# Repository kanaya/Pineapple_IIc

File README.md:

# Pineapple IIc

Edition 2.0.0 for Pineapple IIc 2.0.0

## Congratulations!

You’ve got the latest version of Pineapple Computer named _Pineapple IIc._ But what is Pineapple Computer? Well, it is a MIDI computer that can convert analog signals to MIDI (digital) signal. Now you may want to ask, I guess, what is it for? The Pineapple Computer is an artist-friendly super-easy-to-use computer! You plug power, sensor, MIDI instrument, and boom! Everything is set up.

## How to set up (Hardware)

### Basics

Install the following components.

| Name        | Component         | Note                              |
|-------------|-------------------|-----------------------------------|
| C1          | 47u               |                                   |
| C2          | 10u               |                                   |
| C3-6        | 0.1u              |                                   |
| D1          | 1N4148            |                                   |
| DC12V       | DC Jack           |                                   |
| IC1         | 74LS07            |                                   |
| JP2         | Pinheader 1x3p    | **Bridge top and mid pins**       |
| LED1        | Vf=2.2 If=20m     |                                   |
| MC1         | Arduino Micro 5V  |                                   |
| MIDI-OUT    | DIN 5p            |                                   |
| OK1         | TLP552            |                                   |
| R3-6        | 220               |                                   |
| RN1         | 330               |                                   |
| RN2         | 10k               | Using pin sockets is recommended. |
| SV1         | ML 16p            |                                   |
| VREG1       | 12V to 5V         |                                   |

...To be re-written.

### Non-basic usage

You can drive a relay, I2C devices, and TLC5940 PWM driver by installing some other components on Pineapple IIc. Also you can replace some connectors so that you can use panel mounted connectors and install Pineapple IIc board in a case. For more detail, please read _Extending Pineapple IIc_.

## How to set up (Software)

Install _Pineapple IIc Basic_ sketch to run Pineapple IIc in _Basic_ mode.

## How to play

Connect the following plugs.

* DC---Supply DC 12V to DC Jack connector.
* MIDI---Connect Pineapple IIc's MIDI OUT and your instrument's MIDI IN.
* Sensors---To be written.

## Extending Pineapple IIc

### To use relay

Install the following components as well as _Basic_ components.

| Item        | Name | Spec.      | # |  Note |
|-------------|------|------------|---|-------|
| Transistor  | T1   | 2SC1815    | 1 |       |
| Diode       | D2   | 1N4148     | 1 |       |
| Resistor    | R5-6 | 10k        | 2 |       |
| Relay       | K1   | G5V-1 DC5V | 1 |       |
| Con.        | Relay | PH 3p     | 1 |       |

Also you need to **bridge 7-8 of JP1.**

### To use I2C

Install the following components as well as _Basic_ components.

| Item                   | Name | Spec.      | # |  Note                       |
|------------------------|------|------------|---|-----------------------------|
| Signal level converter | IC2  | PCA9517ADP | 1 | Put A-side up, B-side down. |
| Resistor               | R7-8 | 6.8k       | 2 |                             |
| Con.                   | I2C  | SH 5p      | 1 | D7 operates at **5V.**      |

You need to **un-bridge 1-5, 2-6, 3-7 of JP1.** (D2/SDA and D7 are connected to SW1, and D3PWM/SCL is connected to PWM0 via JP1.)

### To use RST

Install the following components at back side as well as _Basic_ components.

| Item | Name       | Spec.   | # |  Note |
|------|------------|---------|---|-------|
| Con. | RST (Back) | PH 2p   | 1 |       |

### To use LIGHTDRIVE

Install the following components as well as _Basic_ components **except for SW1.** Since Arduino's D8 and D12 pins share SW1 connections and LIGHTDRIVE pins, you need to remove SW1.

| Item | Name       | Spec.        | # |  Note |
|------|------------|--------------|---|-------|
| Con. | LIGHTDRIVE | Pinheader 7p | 1 |       |

The LIGHTDRIVE pinouts are:

| Lightdrive | Meaning | Arduino Pin |
|------------|---------|-------------|
| 1          | Vcc     |             |
| 2          | GND     |             |
| 3          | GSCLCK  | D5PWM       |
| 4          | BLANK   | D8          |
| 5          | XLAT    | D12         |
| 6          | SCLCK   | SCLK        |
| 7          | SIN     | MOSI        |

### To use extra GND pins

Install the following components at back side as well as _Basic_ components.

| Item | Name       | Spec.                 | # |  Note |
|------|------------|-----------------------|---|-------|
| Con. | GND (back) | Pinheader/socket 2x3p | 1 |       |

### To use panel-mounted MIDI connector

Install the following components at back side as well as _Basic_ components.

| Item | Name        | Spec.        | # |  Note |
|------|-------------|--------------|---|-------|
| Con. | MIDI (back) | PH 5p        | 1 |       |

### To use panel-mounted DC Jack

Install one of the following components as well as _Basic_ components.

| Item | Name        | Spec.        | # |  Note |
|------|-------------|--------------|---|-------|
| Con. | PWR1        | Pinheader 2p | 1 |       |
| Con. | PWR2 (back) | PH 2p        | 1 |       |

### To use XOUT

XOUT is designed for extra MIDI OUT capability. It is a direct output of Open Collector so that you may want to install 220-ohm resistor for use as MIDI OUT.

Install the following components as well as _Basic_ components.

| Item | Name | Spec.        | # |  Note |
|------|------|--------------|---|-------|
| Con. | XOUT | Pinheader 5p | 1 |       |

### To use DIGITAL extension

You can hook L1-L7 driver pins by using DIGITAL pins. It also provides +3.3V DC.

Install the following components as well as _Basic_ components.

| Item | Name   | Spec.        | # |  Note |
|------|--------|--------------|---|-------|
| Con. | DIGITL | Pinheader 9p | 1 |       |

### To stack multiple cards

To stack multiple cards, you can do one of the following options.

* Use spacer. _Pineapple IIc_ has four M2 holes at each corners ((3, 3), (88, 3) (88, 52), (3, 52) mm).
* Use Pinheaders of Vcc (bottom left), 3V3 (bottom right), _Pogo_ (top right), Vcc (top left) and perhaps GND (next to the Vcc at top left).

## Technical notes

### Arduino Pinout

| Arduino Micro | Signal     | JP1                               |
|---------------|------------|-----------------------------------|
| RX            | MIDI IN    |                                   |
| TX            | MIDI OUT   |                                   |
| D2/SDA        | SW0/SDA    | 3-4, open to use I2C              |
| D3PWM/SCL     | PWM0/SCL   |                                   |
| D4/A6         | A6         |                                   |
| D5PWM         | PWM1       |                                   |
| D6PWM/A7      | PWM2       |                                   |
| D7            | SW1        | 5-6, open to use D7 independently |
| D8/A8         | SW2        |                                   |
| D9PWM/A9      | PWM3       |                                   |
| D10PWM/A10    | PWM4       |                                   |
| D11PWM        | PWM5       |                                   |
| D12/A11       | SW3        |                                   |
| D13PWM        | PWM6/Relay | 7-8, close to use relay           |
| A0-5          | A0-5       |                                   |

### JP1 Pinout

| JP1 | Signal                 | JP1 | Signal |
|-----|------------------------|-----|--------|
| 1   | Level Converter Enable | 2   | GND    |
| 3   | D2SDA (SW0/SDA)        | 4   | SW0    |
| 5   | D7 (SW1)               | 6   | SW1    |
| 7   | D13PWM (PWM6/Relay)    | 8   | Relay  |

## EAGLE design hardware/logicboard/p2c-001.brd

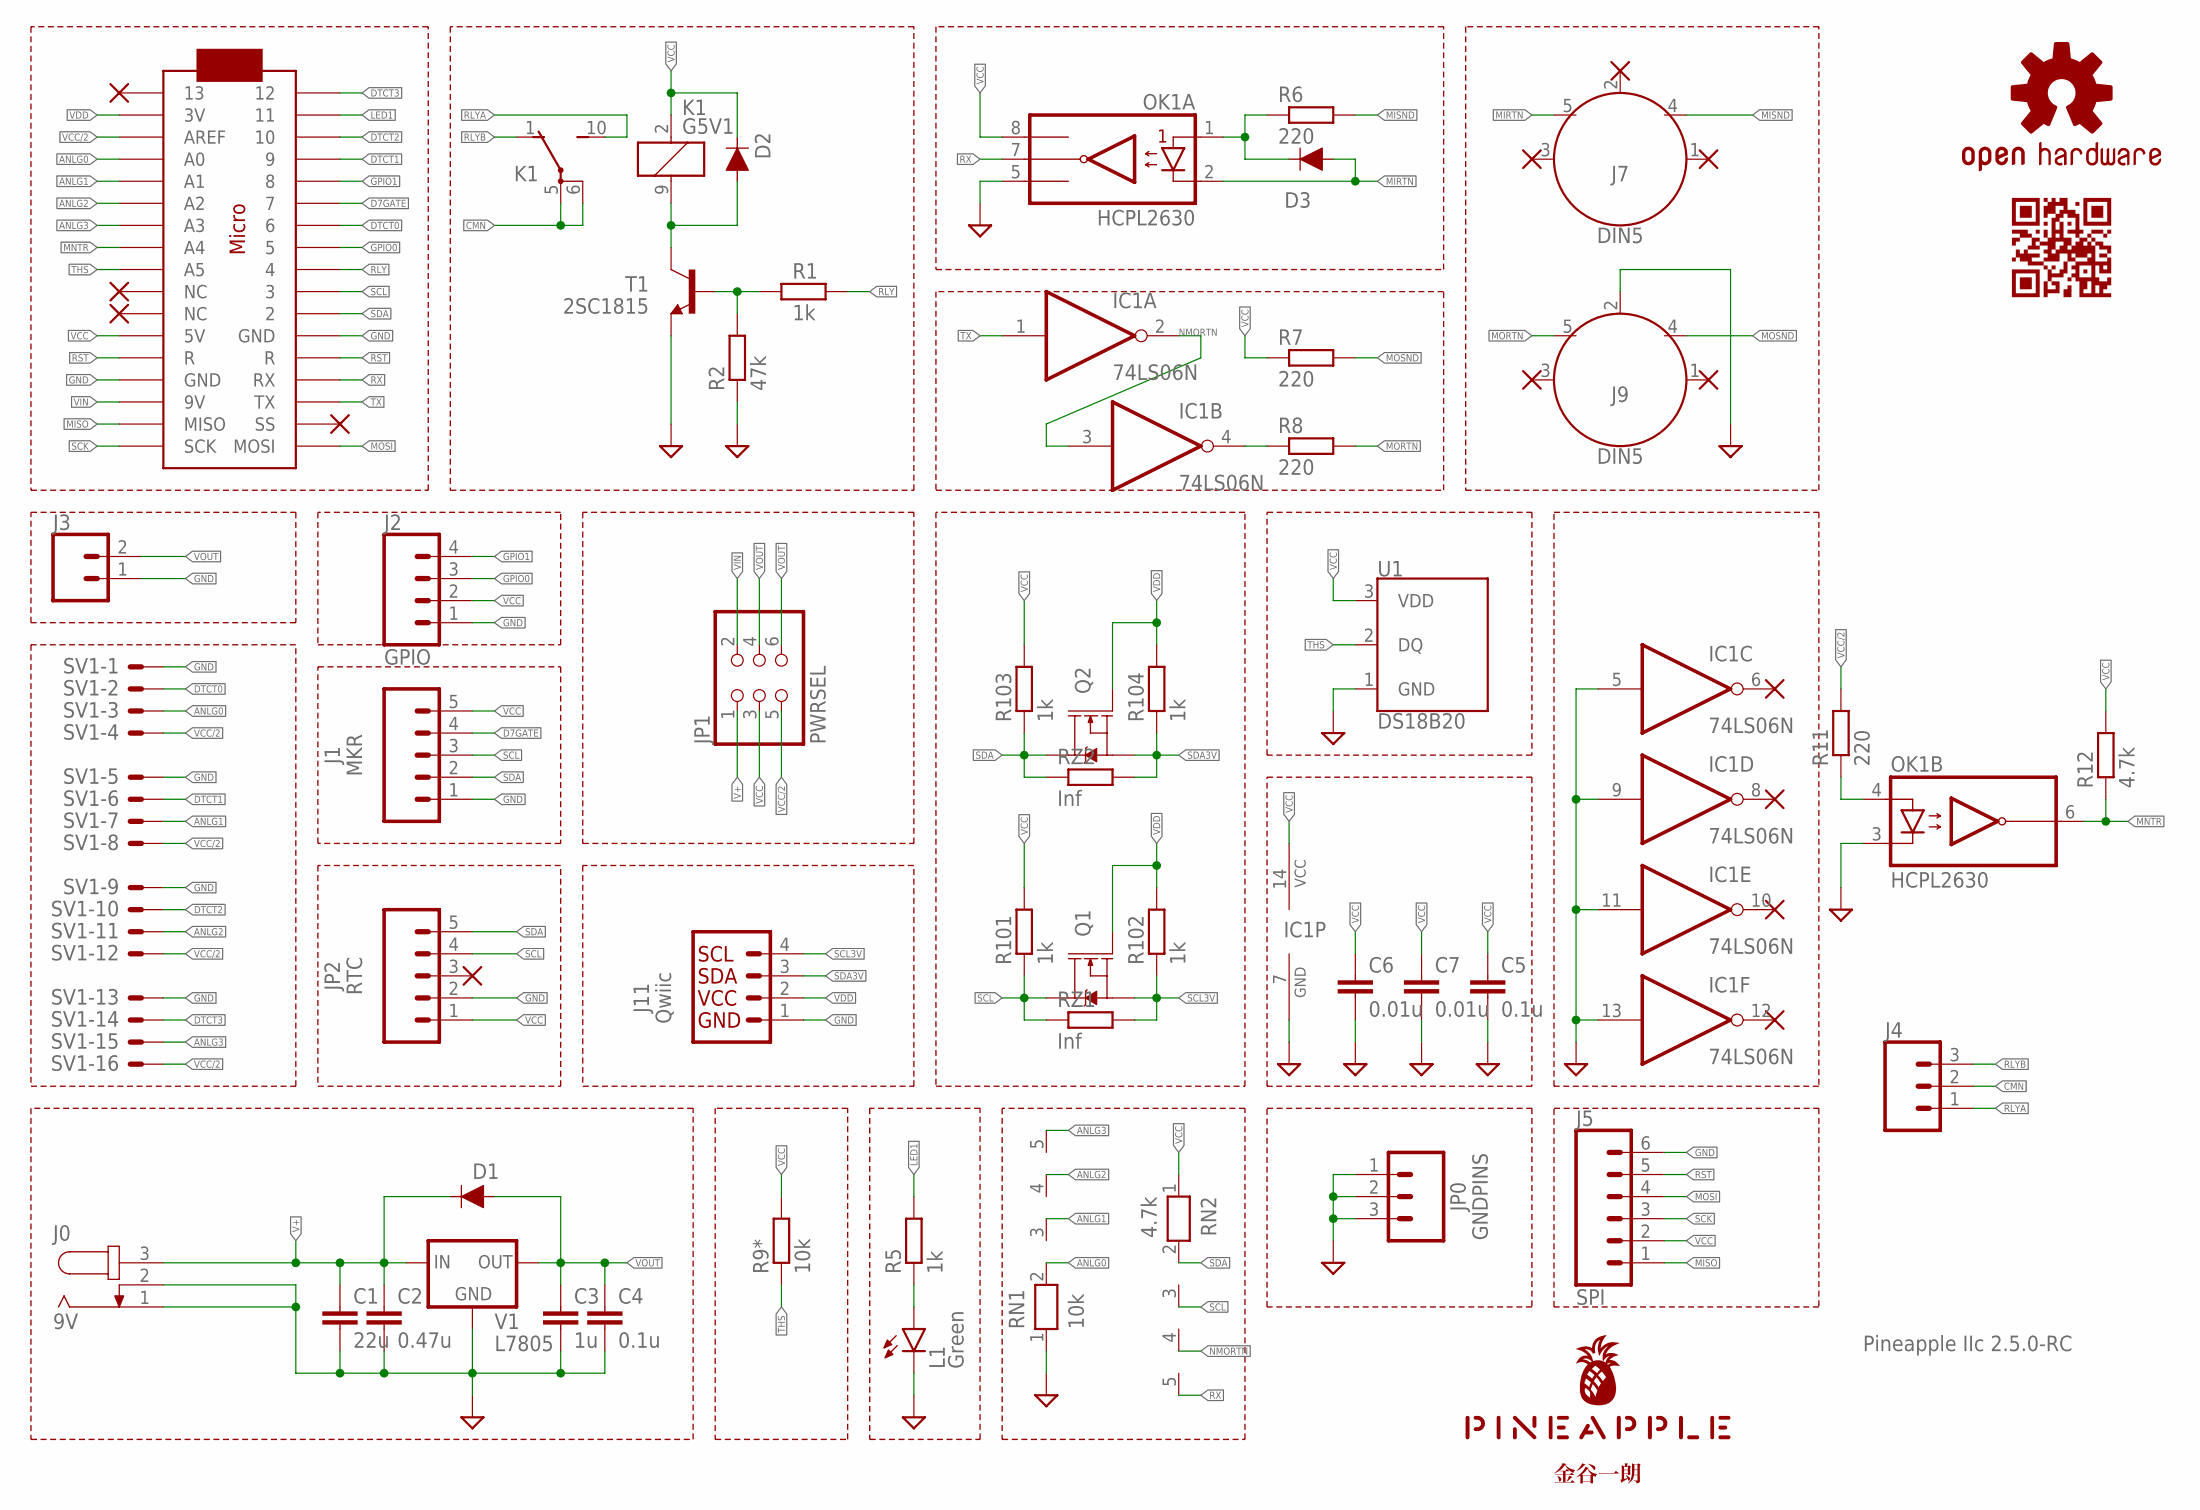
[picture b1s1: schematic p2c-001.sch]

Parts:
C1: 22u; C025-050X050
C2: 0.47u; C050-024X044
C3: 1u; C050-024X044
C4, C5: 0.1u; C025-024X044
C6, C7: 0.01u; C025-024X044
D1, D2, D3: DIODE-1N4148
IC1: 74LS06N; DIL14
J0: 9V; SPC4077
J1: MKR; JST-5-PTH
J2: GPIO; JST-4-PTH
J3: CONN_02JST-PTH-2; JST-2-PTH
J4: CONN_03JST-PTH-NS; JST-3-PTH-NS
J5: SPI; 1X06_1.27MM
J7, J9: DIN5; DIN5-RA-PTH
J11: Qwiic; 1X04_1MM_RA
JP0: GNDPINS; 1X03
JP1: PWRSEL; 2X03
JP2: RTC; 1X05
K1: G5V1
L1: Green; LED3MM
LOGO1: OSHW-LOGOS-COPPER; OSHW-LOGO-S_COPPER
OK1: HCPL2630; DIL08
Q1, Q2: 220mA/50V/3.5Ω; SOT23-3
R1, R5: 1k; 0204/5
R2: 47k; 0204/5
R6, R7, R8, R11: 220; 0204/5
R9*: 10k; 0204/5
R12: 4.7k; 0204/5
R101, R102, R103, R104: 1k; R2012
RN1: 10k; RN-5
RN2: 4.7k; RN-5
RZ1, RZ2: Inf; R2012
SV1: ML16LE; ML16L
T1: 2SC1815; TO92-ECB
U1: DS18B20; TO-92-AMMO
U$1: PINEAPPLE450_SILK
U$2: ARDUINOMICRO
U$3: KANAYA768_SILK
U$4: CARDQRCODE450_SILK
V1: L7805; 78XXS

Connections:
ANLG0: RN1.2, SV1.3, U$2.P$31 (A0)
ANLG1: RN1.3, SV1.7, U$2.P$30 (A1)
ANLG2: RN1.4, SV1.11, U$2.P$29 (A2)
ANLG3: RN1.5, SV1.15, U$2.P$28 (A3)
CMN: J4.2, K1.5, K1.6
D7GATE: J1.4, U$2.P$6 (7)
DTCT0: SV1.2, U$2.P$7 (6)
DTCT1: SV1.6, U$2.P$4 (9)
DTCT2: SV1.10, U$2.P$3 (10)
DTCT3: SV1.14, U$2.P$1 (12)
GND: C1.2, C2.2, C3.2, C4.2, C5.2, C6.2, C7.2, IC1.5 (I), IC1.7 (GND), IC1.9 (I), IC1.11 (I), IC1.13 (I), J0.1, J0.2, J1.1, J2.1, J3.1, J5.6, J9.2, J11.1 (GND), JP0.1, JP0.2, JP0.3, JP2.2, L1.K (C), OK1.3 (C2), OK1.5 (GND), R2.1, RN1.1, SV1.1, SV1.5, SV1.9, SV1.13, T1.E, U1.1 (GND), U$2.P$12 (GND), U$2.P$21 (GND), V1.GND
GPIO0: J2.3, U$2.P$8 (5)
GPIO1: J2.4, U$2.P$5 (8)
LED1: R5.2, U$2.P$2 (11)
LED1A: L1.A, R5.1
MIA: D3.C, OK1.1 (A1), R6.1
MIRTN: D3.A, J7.5, OK1.2 (C1)
MISND: J7.4, R6.2
MISO: J5.1, U$2.P$19 (MISO)
MNTR: OK1.6 (VO2), R12.1, U$2.P$27 (A4)
MNTRA: OK1.4 (A2), R11.1
MORTN: J9.5, R8.2
MORTNRAW: IC1.4 (O), R8.1
MOSI: J5.4, U$2.P$17 (MOSI)
MOSND: J9.4, R7.2
NMORTN: IC1.2 (O), IC1.3 (I), RN2.4
RLY: R1.2, U$2.P$9 (4)
RLYA: J4.1, K1.10 (S)
RLYB: J4.3, K1.1 (O)
RLYC: D2.A, K1.9 (2), T1.C
RLYQ: R1.1, R2.2, T1.B
RST: J5.5, U$2.P$13 (R), U$2.P$22 (R)
RX: OK1.7 (VO1), RN2.5, U$2.P$14 (RX)
SCK: J5.3, U$2.P$18 (SCK)
SCL: J1.3, JP2.4, Q1.3 (D), R101.1, RN2.3, RZ1.1, U$2.P$10 (3)
SCL3V: J11.4 (SCL), Q1.2 (S), R102.1, RZ1.2
SDA: J1.2, JP2.5, Q2.3 (D), R103.1, RN2.2, RZ2.1, U$2.P$11 (2)
SDA3V: J11.3 (SDA), Q2.2 (S), R104.1, RZ2.2
THS: R9*.1, U1.2 (DQ), U$2.P$26 (A5)
TX: IC1.1 (I), U$2.P$15 (TX)
V+: C1.1, C2.1, D1.C, J0.3, JP1.1, V1.IN
VCC: C5.1, C6.1, C7.1, D2.C, IC1.14 (VCC), J1.5, J2.2, J5.2, JP1.3, JP2.1, K1.2 (1), OK1.8 (VCC), R7.1, R9*.2, R12.2, R101.2, R103.2, RN2.1, U1.3 (VDD), U$2.P$23 (5V)
VCC/2: JP1.5, R11.2, SV1.4, SV1.8, SV1.12, SV1.16, U$2.P$32 (AREF)
VDD: J11.2 (VCC), Q1.1 (G), Q2.1 (G), R102.2, R104.2, U$2.P$33 (3V)
VIN: JP1.2, U$2.P$20 (9V)
VOUT: C3.1, C4.1, D1.A, J3.2, JP1.4, JP1.6, V1.OUT

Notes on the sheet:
Pineapple IIc 2.5.0-RC

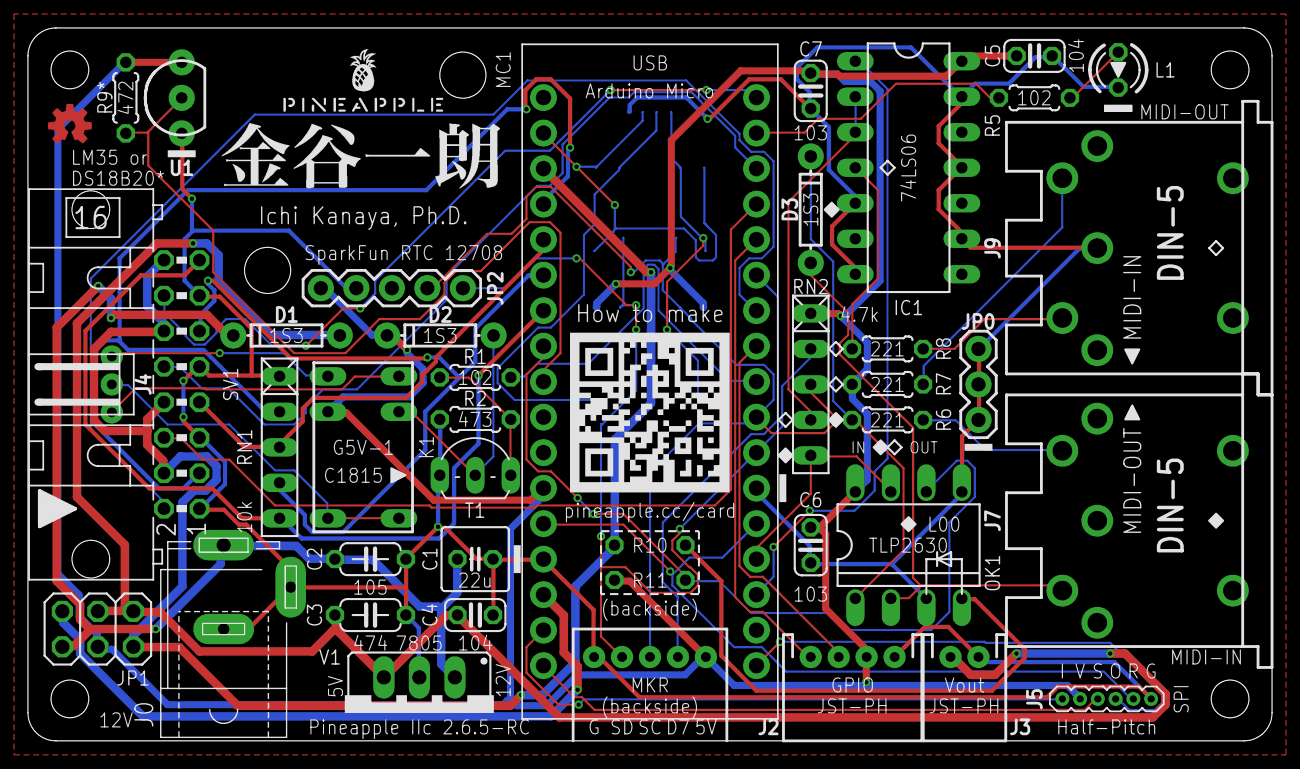
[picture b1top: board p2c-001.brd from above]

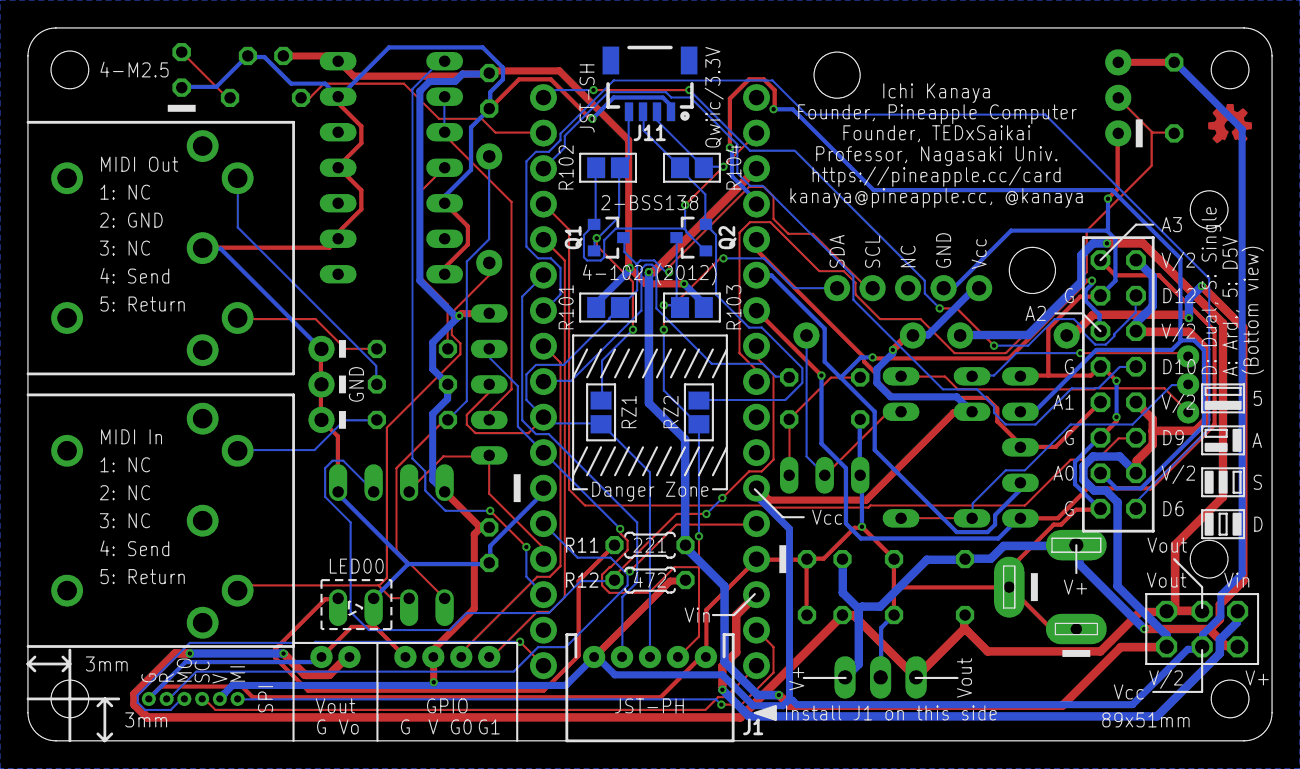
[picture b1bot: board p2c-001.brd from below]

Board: 2 copper layers, 89.0 x 51.0 mm, 56 parts (12 on the bottom side), 46 nets.

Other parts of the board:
U$5, U$6: STAND-OFF

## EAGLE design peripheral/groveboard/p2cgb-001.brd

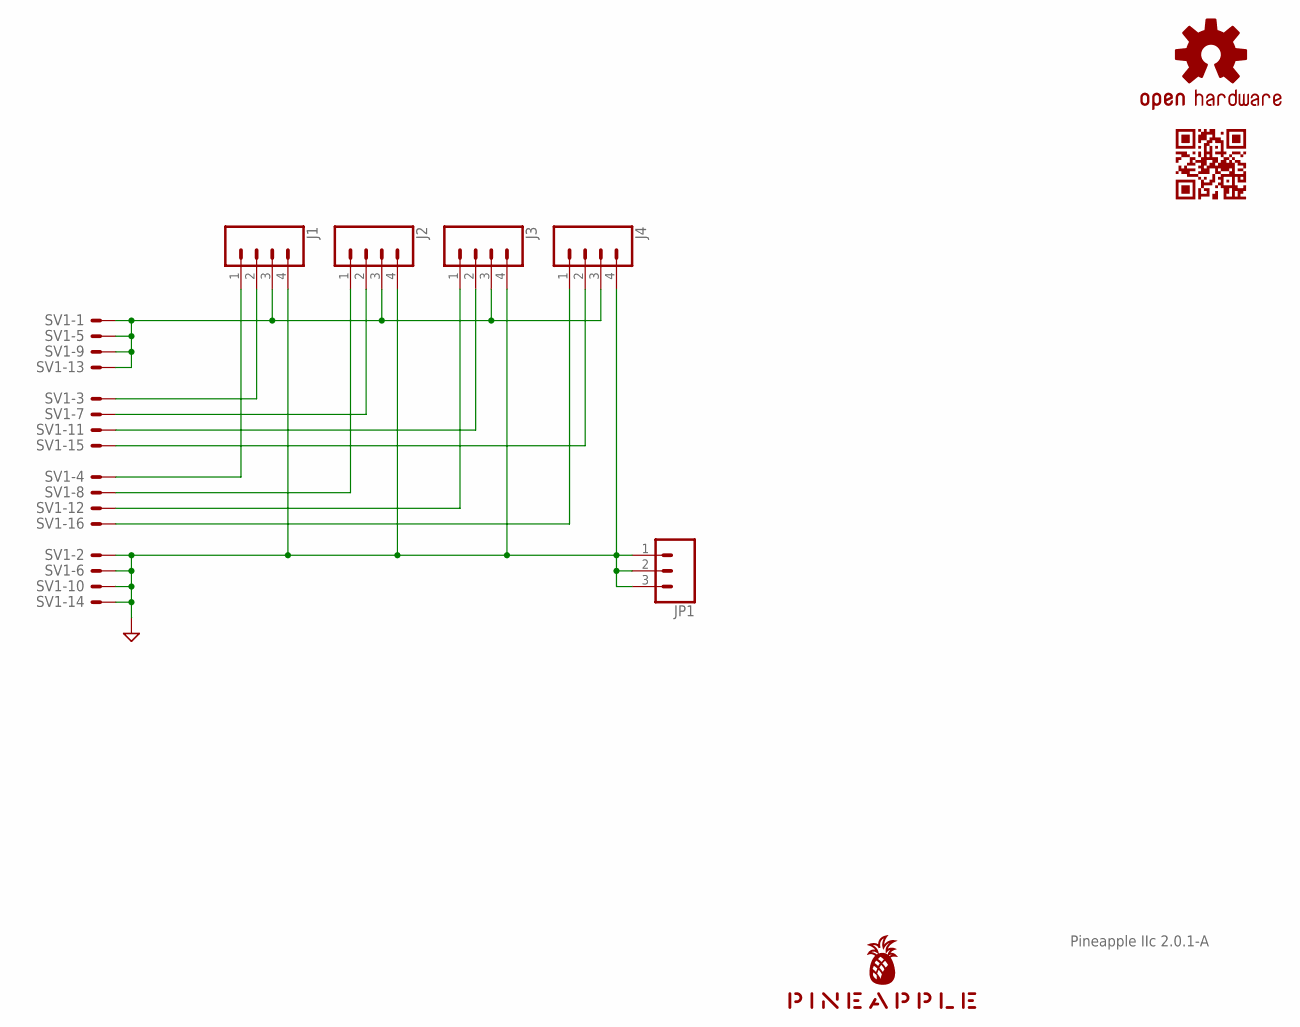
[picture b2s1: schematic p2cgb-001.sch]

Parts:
J1, J2, J3, J4: CONN_04JST-PTH; JST-4-PTH
JP1: CONN_03; 1X03
LOGO1: OSHW-LOGOS-COPPER; OSHW-LOGO-S_COPPER
SV1: ML16LE; ML16L
U$1: PINEAPPLE450_SILK
U$4: CARDQRCODE450_SILK

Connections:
GND: J1.4, J2.4, J3.4, J4.4, JP1.1, JP1.2, JP1.3, SV1.2, SV1.6, SV1.10, SV1.14
unnamed: J1.1, SV1.4
unnamed: J2.1, SV1.8
unnamed: J3.1, SV1.12
unnamed: J4.1, SV1.16
unnamed: J1.2, SV1.3
unnamed: J2.2, SV1.7
unnamed: J3.2, SV1.11
unnamed: J4.2, SV1.15
VCC: J1.3, J2.3, J3.3, J4.3, SV1.1, SV1.5, SV1.9, SV1.13

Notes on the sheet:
Pineapple IIc 2.0.1-A

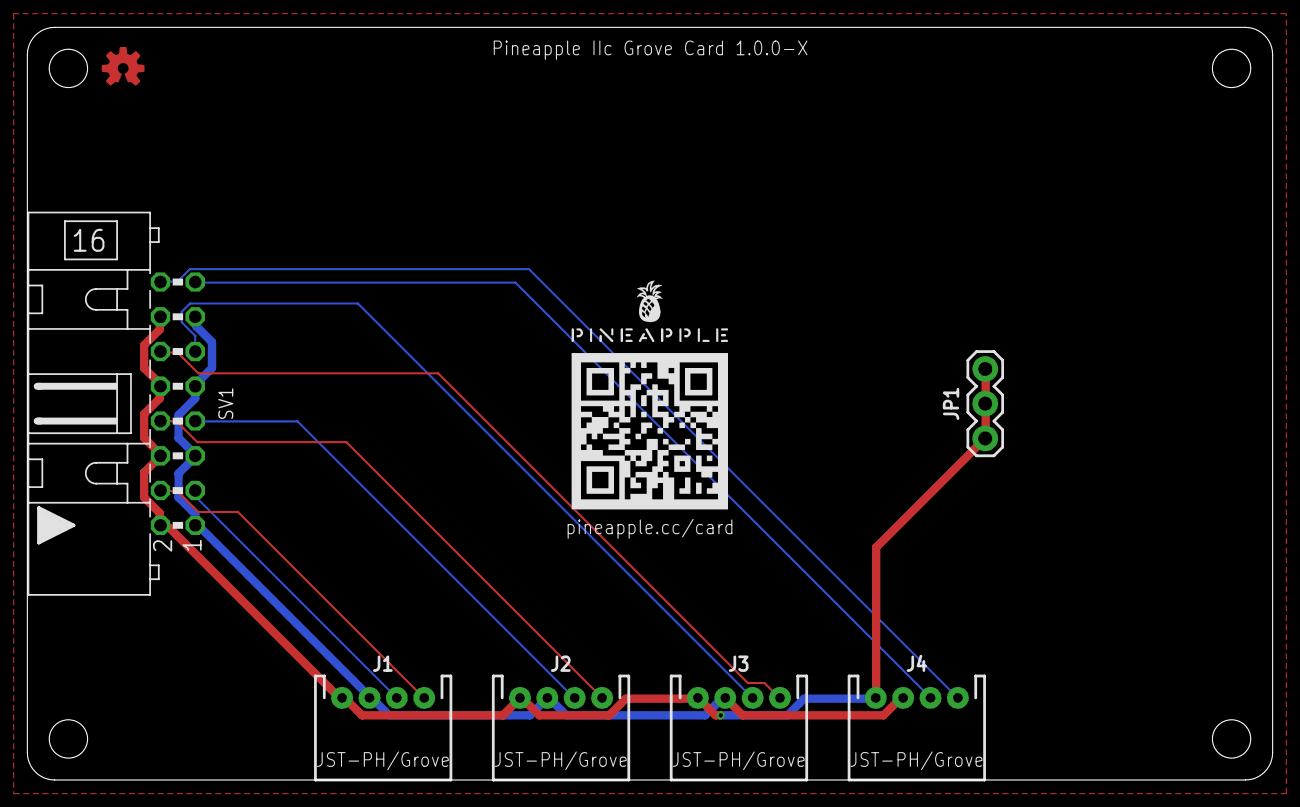
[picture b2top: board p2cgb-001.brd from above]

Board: 2 copper layers, 91.0 x 55.0 mm, 9 parts (0 on the bottom side), 10 nets.

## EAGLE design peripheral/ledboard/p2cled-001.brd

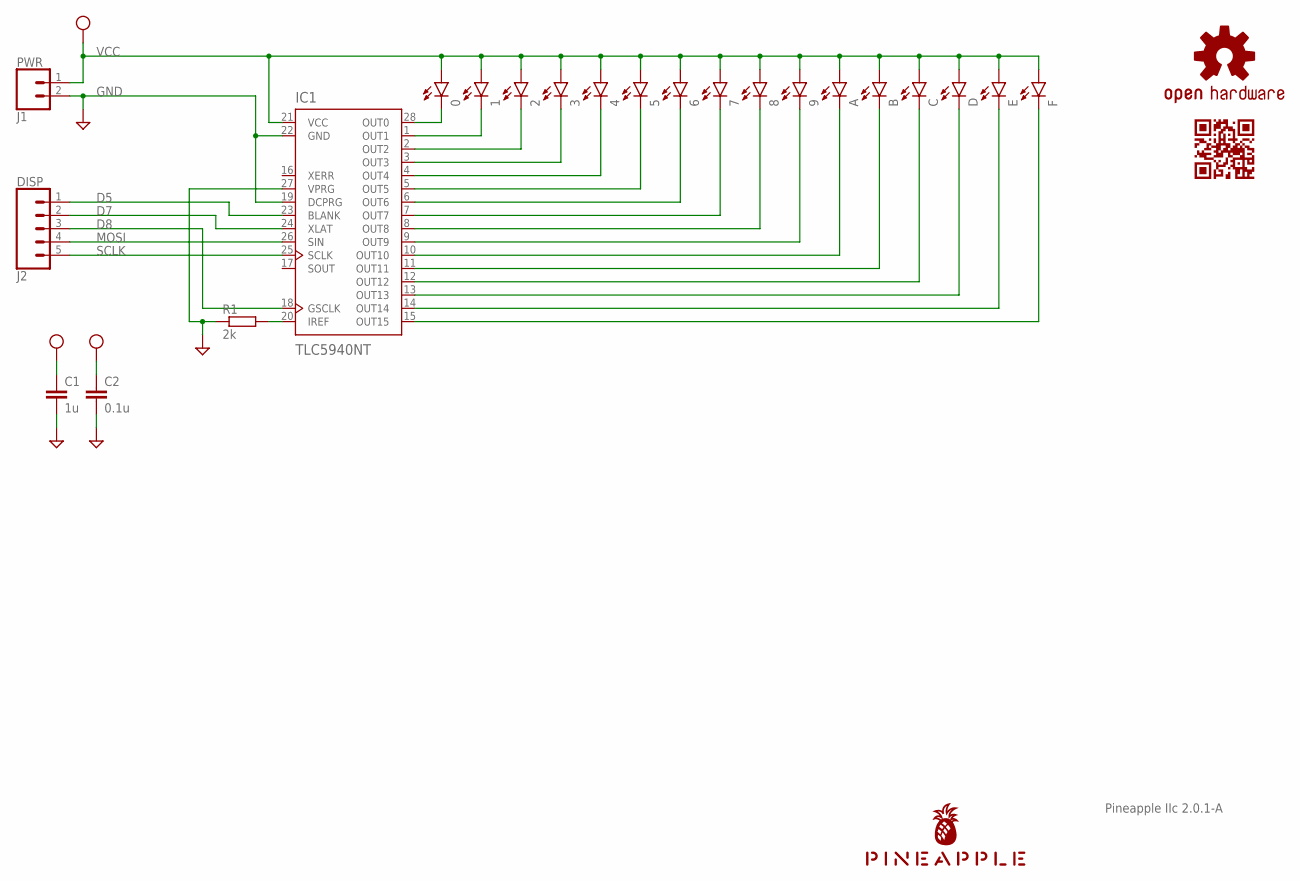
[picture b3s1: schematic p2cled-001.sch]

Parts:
0, 1, 2, 3, 4, 5, 6, 7, 8, 9: LEDB152; Q62902-B152
A: LEDB152; Q62902-B152
B: LEDB152; Q62902-B152
C: LEDB152; Q62902-B152
C1: 1u; C025-024X044
C2: 0.1u; C025-024X044
D: LEDB152; Q62902-B152
E: LEDB152; Q62902-B152
F: LEDB152; Q62902-B152
IC1: TLC5940NT; DIL28-3
J1: PWR; JST-2-PTH
J2: DISP; JST-5-PTH
LOGO1: OSHW-LOGOS-COPPER; OSHW-LOGO-S_COPPER
R1: 2k; 0204/5
U$1: PINEAPPLE450_SILK
U$4: CARDQRCODE450_SILK

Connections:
D5: IC1.23 (BLANK), J2.1
D7: IC1.24 (XLAT), J2.2
D8: IC1.18 (GSCLK), J2.3
MOSI: IC1.26 (SIN), J2.4
unnamed: 0.K (C), IC1.28 (OUT0)
unnamed: 1.K (C), IC1.1 (OUT1)
unnamed: 2.K (C), IC1.2 (OUT2)
unnamed: 3.K (C), IC1.3 (OUT3)
unnamed: 4.K (C), IC1.4 (OUT4)
unnamed: 5.K (C), IC1.5 (OUT5)
unnamed: 6.K (C), IC1.6 (OUT6)
unnamed: 7.K (C), IC1.7 (OUT7)
unnamed: 8.K (C), IC1.8 (OUT8)
unnamed: 9.K (C), IC1.9 (OUT9)
unnamed: A.K (C), IC1.10 (OUT10)
unnamed: B.K (C), IC1.11 (OUT11)
unnamed: C.K (C), IC1.12 (OUT12)
unnamed: D.K (C), IC1.13 (OUT13)
unnamed: E.K (C), IC1.14 (OUT14)
unnamed: F.K (C), IC1.15 (OUT15)
unnamed: IC1.20 (IREF), R1.2
SCLK: IC1.25 (SCLK), J2.5

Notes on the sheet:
Pineapple IIc 2.0.1-A

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
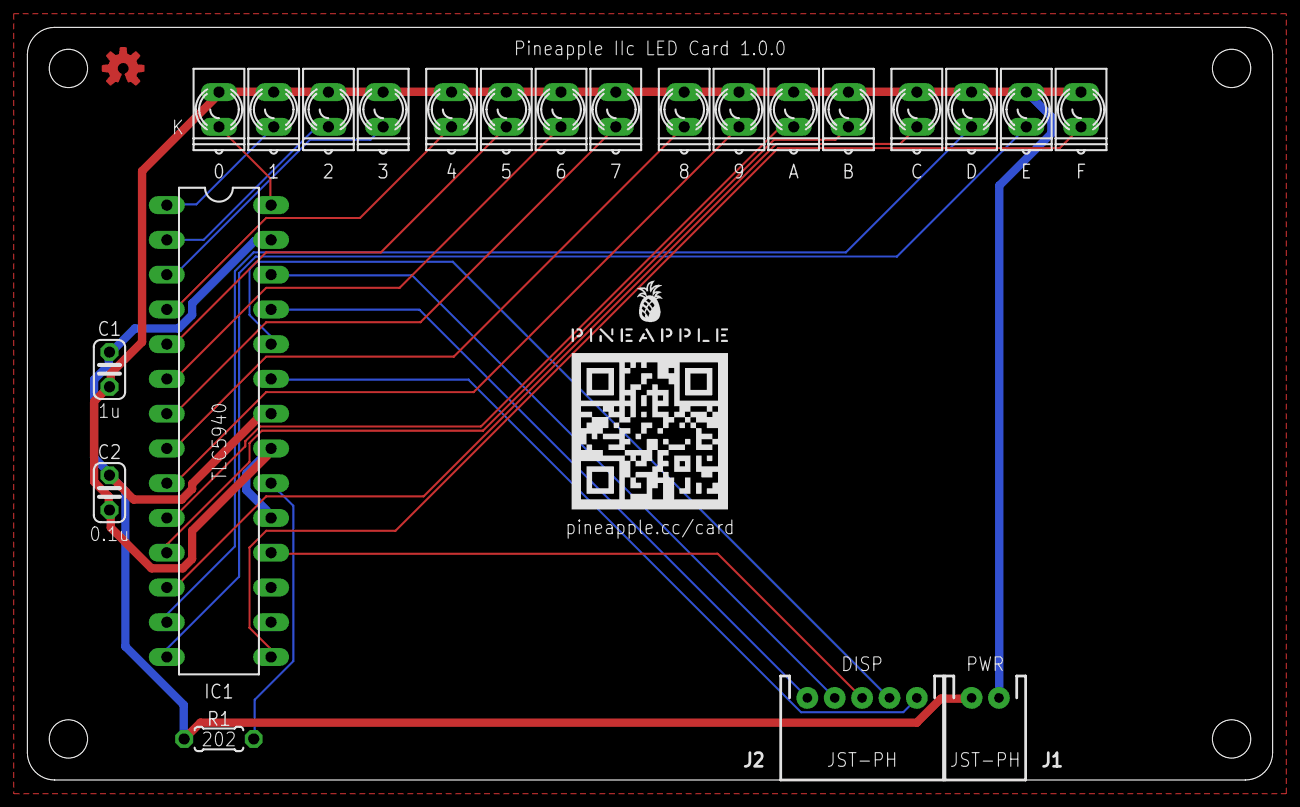
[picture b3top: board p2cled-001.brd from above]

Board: 2 copper layers, 91.0 x 55.0 mm, 25 parts (0 on the bottom side), 24 nets.

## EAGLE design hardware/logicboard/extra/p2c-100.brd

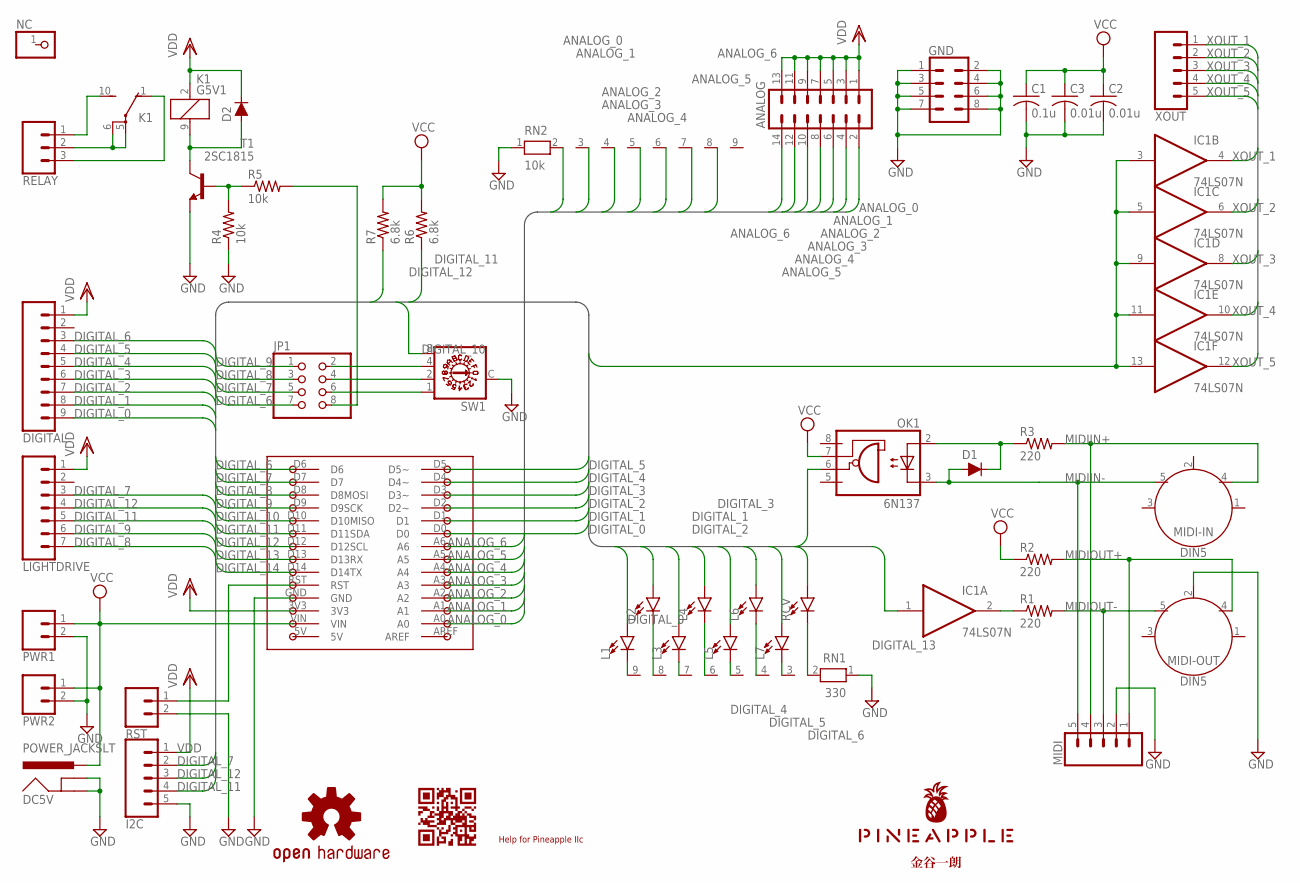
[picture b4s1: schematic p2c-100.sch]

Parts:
ANALOG: ML14L
C1: 0.1u; C025-025X050
C2, C3: 0.01u; C025-024X044
D1, D2: DIODE-1N4148
DC5V: POWER_JACKSLT; POWER_JACK_SLOT
DIGITAL: CONN_09; 1X09
GND: CONN_04X2; 2X4
I2C: CONN_05SMD2; 1X05_1MM_RA
IC1: 74LS07N; DIL14
JP1: PINHD-2X4; 2X04
K1: G5V1
L1, L2, L3, L4, L5, L6, L7: LED-3MM-NO_SILK; LED_3MM-NS
LIGHTDRIVE: CONN_07; 1X07
LOGO1: OSHW-LOGOS-COPPER; OSHW-LOGO-S_COPPER
MIDI: CONN_05JST; JST-5-PTH
MIDI-IN: DIN5; DIN5-RA-PTH
MIDI-OUT: DIN5; DIN5-RA-PTH
NC: PINHD-1X1; 1X01
OK1: 6N137; DIL08
PWR1: CONN_02; 1X02
PWR2: CONN_02JST-PTH-2; JST-2-PTH
R1, R2, R3: 220; 0204/5
R4, R5: 10k; 0204/5
R6, R7: 6.8k; 0204/5
RCV: LED-3MM-NO_SILK; LED_3MM-NS
RELAY: CONN_03JST-PTH; JST-3-PTH
RN1: 330; RN-9
RN2: 10k; RN-9
RST: CONN_02JST-PTH-2; JST-2-PTH
SW1: A1353HEX
T1: 2SC1815; TO92-ECB
U1: MKR1000
U$1: PINEAPPLE450_SILK
U$3: KANAYA768_SILK
U$4: CARDQRCODE450_SILK
U$5: HELP_P2C
XOUT: CONN_05; 1X05

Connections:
ANALOG_0: ANALOG.2, RN2.2, U1.A0
ANALOG_1: ANALOG.4, RN2.3, U1.A1
ANALOG_2: ANALOG.6, RN2.4, U1.A2
ANALOG_3: ANALOG.8, RN2.5, U1.A3
ANALOG_4: ANALOG.10, RN2.6, U1.A4
ANALOG_5: ANALOG.12, RN2.7, U1.A5
ANALOG_6: ANALOG.14, RN2.8, U1.A6
DIGITAL_0: DIGITAL.9, L1.A, U1.D0
DIGITAL_1: DIGITAL.8, L2.A, U1.D1
DIGITAL_2: DIGITAL.7, L3.A, U1.D2 (D2~)
DIGITAL_3: DIGITAL.6, L4.A, U1.D3 (D3~)
DIGITAL_4: DIGITAL.5, L5.A, U1.D4 (D4~)
DIGITAL_5: DIGITAL.4, L6.A, U1.D5 (D5~)
DIGITAL_6: DIGITAL.3, JP1.7, L7.A, U1.D6
DIGITAL_7: I2C.2, JP1.5, LIGHTDRIVE.3, U1.D7
DIGITAL_8: JP1.3, LIGHTDRIVE.7, U1.D8 (D8MOSI)
DIGITAL_9: JP1.1, LIGHTDRIVE.6, U1.D9 (D9SCK)
DIGITAL_10: SW1.8, U1.D10 (D10MISO)
DIGITAL_11: I2C.4, LIGHTDRIVE.5, R6.1, U1.D11 (D11SDA)
DIGITAL_12: I2C.3, LIGHTDRIVE.4, R7.1, U1.D12 (D12SCL)
DIGITAL_13: OK1.6 (VO), RCV.A, U1.D13 (D13RX)
DIGITAL_14: IC1.1 (I), IC1.3 (I), IC1.5 (I), IC1.9 (I), IC1.11 (I), IC1.13 (I), U1.D14 (D14TX)
GND: C1.2, C2.2, C3.2, DC5V.GND@1 (GNDBREAK), DC5V.GND@2 (GND), GND.1, GND.2, GND.3, GND.4, GND.5, GND.6, GND.7, GND.8, I2C.5, IC1.7 (GND), MIDI.2, MIDI-OUT.2, PWR1.2, PWR2.2, R4.1, RN1.1, RN2.1, RST.2, SW1.C, T1.E, U1.GND
MIDIIN+: MIDI.4, MIDI-IN.4, R3.2
MIDIIN-: D1.A, MIDI.5, MIDI-IN.5, OK1.3 (C)
MIDIINA: D1.C, OK1.2 (A), R3.1
MIDIOUT+: MIDI.1, MIDI-OUT.4, R2.2
MIDIOUT-: MIDI.3, MIDI-OUT.5, R1.2
MIDIOUTC: IC1.2 (O), R1.1
unnamed: L1.K (C), RN1.9
unnamed: RST.1, U1.RST
unnamed: JP1.8, R5.2
unnamed: JP1.6, SW1.1
unnamed: JP1.4, SW1.2
unnamed: JP1.2, SW1.4
unnamed: L2.K (C), RN1.8
unnamed: L3.K (C), RN1.7
unnamed: L4.K (C), RN1.6
unnamed: L5.K (C), RN1.5
unnamed: L6.K (C), RN1.4
unnamed: L7.K (C), RN1.3
unnamed: RCV.K (C), RN1.2
RELAYCOM: K1.5, K1.6, RELAY.2
RELAYDRIVE: R4.2, R5.1, T1.B
RELAYNC: K1.1 (O), RELAY.3
RELAYNO: K1.10 (S), RELAY.1
RELAYTR: D2.A, K1.9 (2), T1.C
VCC: C1.1, C2.1, C3.1, DC5V.PWR, IC1.14 (VCC), OK1.7 (VE), PWR1.1, PWR2.1, R2.1, R6.2, R7.2, U1.VIN
VDD: ANALOG.1, ANALOG.3, ANALOG.5, ANALOG.7, ANALOG.9, ANALOG.11, ANALOG.13, D2.C, DIGITAL.1, I2C.1, K1.2 (1), LIGHTDRIVE.1, U1.3V3
XOUT_1: IC1.4 (O), XOUT.1
XOUT_2: IC1.6 (O), XOUT.2
XOUT_3: IC1.8 (O), XOUT.3
XOUT_4: IC1.10 (O), XOUT.4
XOUT_5: IC1.12 (O), XOUT.5

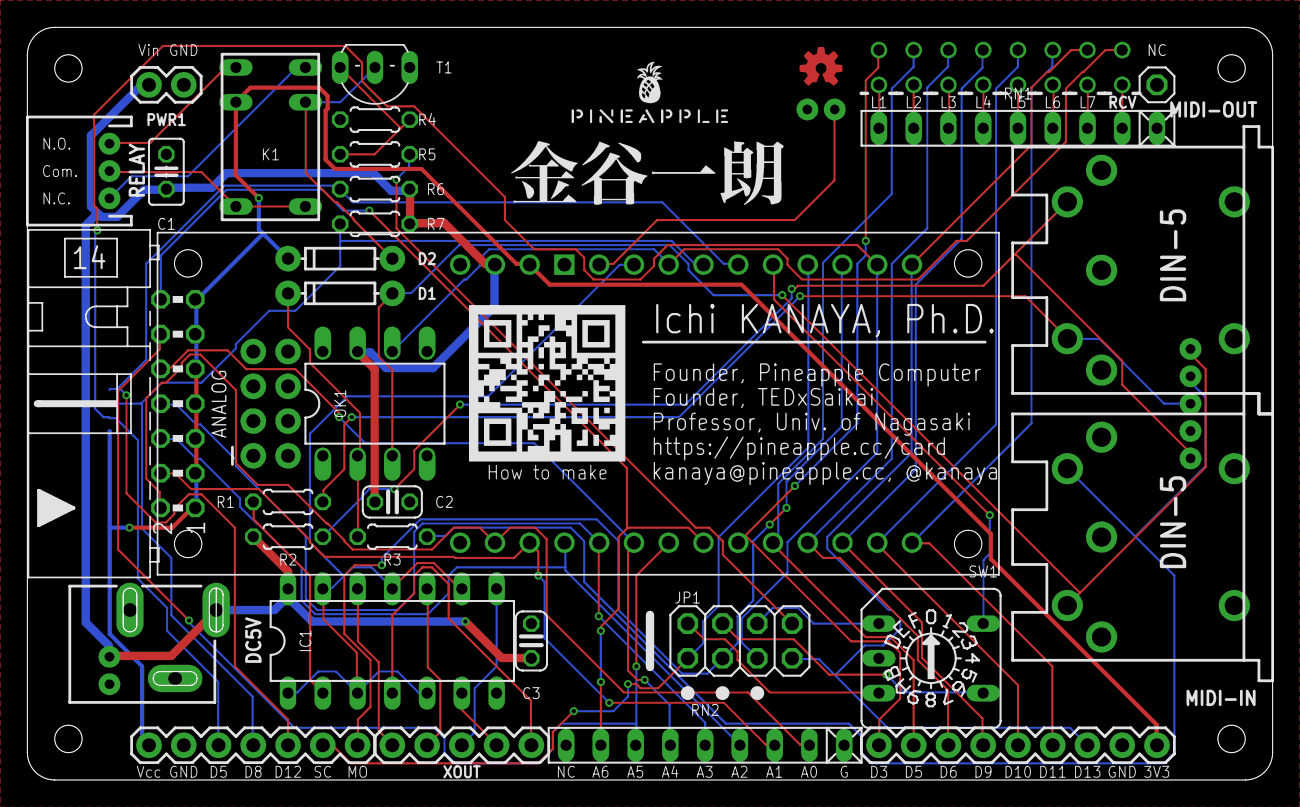
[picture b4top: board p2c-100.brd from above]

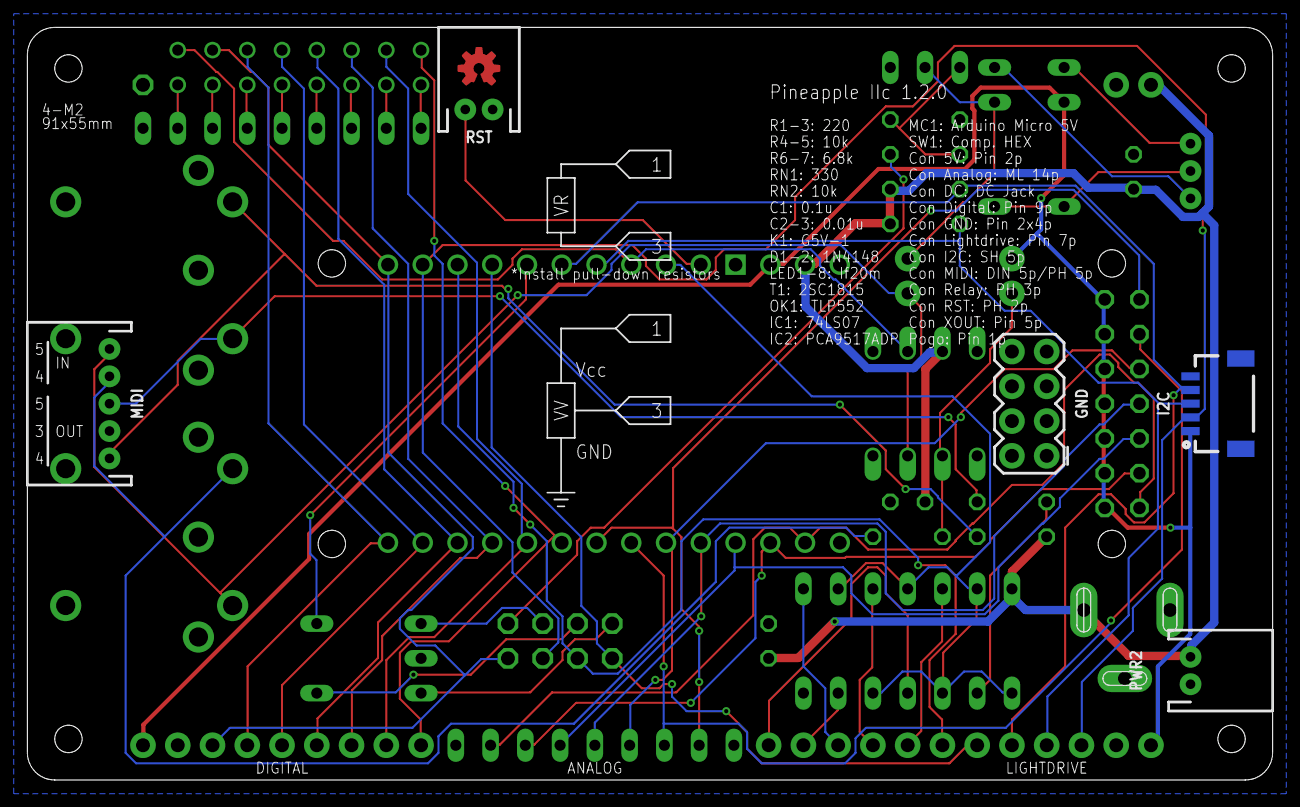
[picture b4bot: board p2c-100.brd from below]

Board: 2 copper layers, 91.0 x 55.0 mm, 49 parts (6 on the bottom side), 54 nets.

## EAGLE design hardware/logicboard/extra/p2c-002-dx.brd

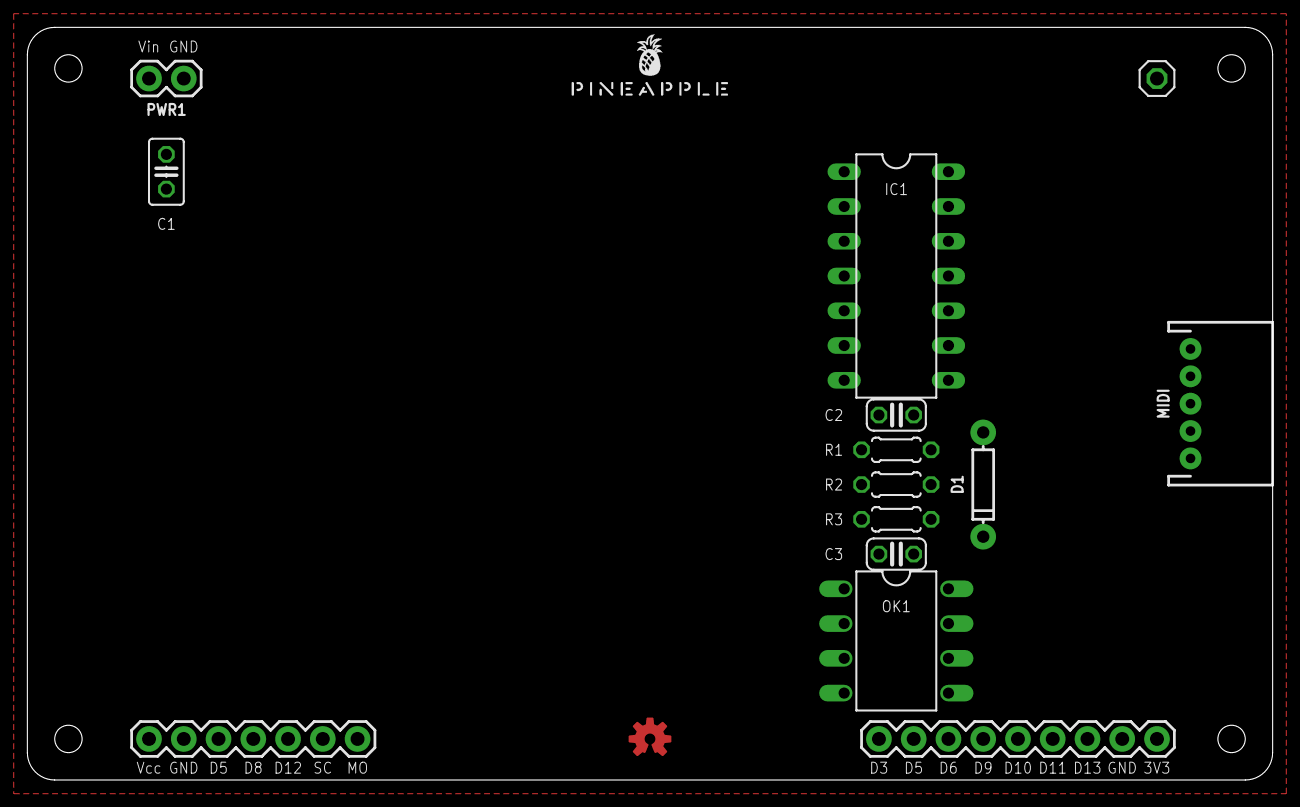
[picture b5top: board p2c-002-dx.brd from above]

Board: 2 copper layers, 91.0 x 55.0 mm, 16 parts (0 on the bottom side), 5 nets, no tracks yet.

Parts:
C1: 0.1u; C025-025X050
C2, C3: 0.01u; C025-024X044
D1: DIODE-1N4148
DIGITAL: 1X09
IC1: 74LS07N; DIL14
LIGHTDRIVE: 1X07
LOGO1: OSHW-LOGOS-COPPER; OSHW-LOGO-S_COPPER
MIDI: JST-5-PTH
OK1: 6N137; DIL08
POGOPIN: 1X01
PWR1: 1X02
R1, R2, R3: 220; 0204/5
U$1: PINEAPPLE450_SILK

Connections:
GND: C1.2, C2.2, C3.2, IC1.3, IC1.5, IC1.7, IC1.9, IC1.11, IC1.13
MIDIIN-: D1.A, OK1.3
MIDIINA: D1.C, OK1.2, R3.1
MIDIOUTC: IC1.2, R1.1
VCC: C1.1, C2.1, C3.1, IC1.14, OK1.7, R2.1

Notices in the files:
parts and their libraries:
SparkFun-Connectors: Licensing: Creative Commons ShareAlike 4.0 International - https://creativecommons.org/licenses/by-sa/4.0
